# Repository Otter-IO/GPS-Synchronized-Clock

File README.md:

# GPS-Synchronized-Clock
This is an FPGA based GPS Synchronized Clock. It utilizes an Intel 10M02SCE144 single supply FPGA with integrated configuration memory.

The clock is split into 2 pieces, the FPGA board and the clock display. This was done so that to FPGA board could be used for other projects easily without redesign. It also allowed me to use a 4-layer board for the FPGA and a 2-layer board for the clock display. This helped keep costs low while also getting the advantages of a 4-layer board for the FPGA. The boards were designed using KiCAD.

The code is written in Verilog and is split into multiple modules to allow for easy modification and reuse. The bitstream files for the FPGA were generated using the free version of Intel Quartus Prime. The entire project is included for your use.

The code is by no means perfect. I’m still learning Verilog and there are certainly optimizations that could be made, especially with the SDC timing file. If you have more experience with FPGAs feel free to improve the design.

See the final product on YouTube: https://www.youtube.com/watch?v=TpDHRGk3vro

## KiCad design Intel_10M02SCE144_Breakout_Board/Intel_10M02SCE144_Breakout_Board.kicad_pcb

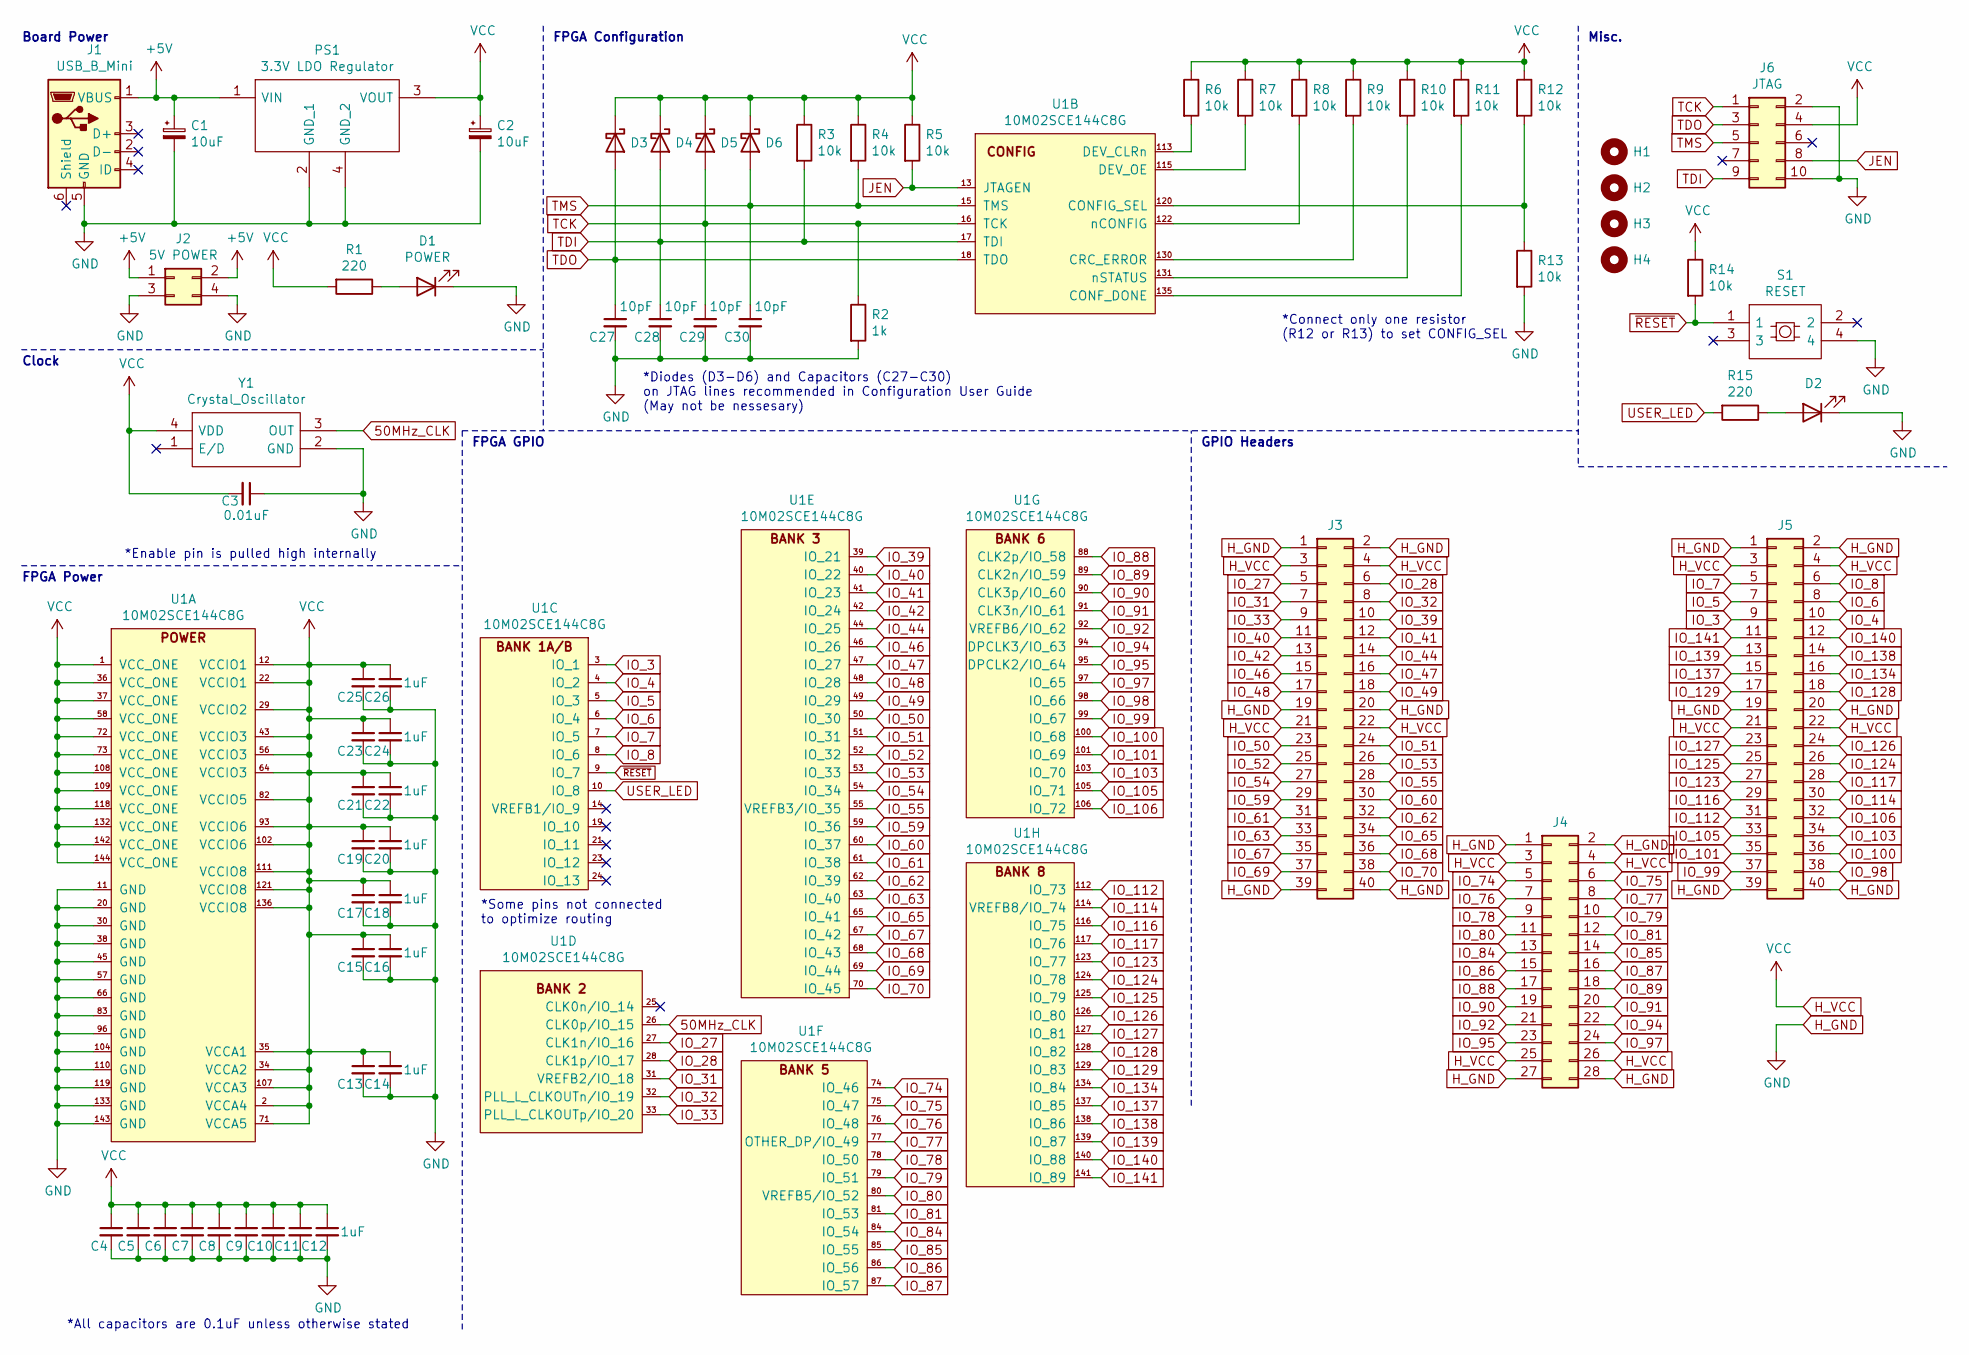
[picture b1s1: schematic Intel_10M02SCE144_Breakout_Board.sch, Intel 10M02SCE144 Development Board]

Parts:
C1, C2: 10uF; CP_Radial_D4.0mm_P2.00mm
C3: 0.01uF; C_0603_1608Metric_Pad1.08x0.95mm_HandSolder
C4, C5, C6, C7, C8, C9, C10, C11, C13, C15, C17, C19, C21, C23, C25: 0.1uF; C_0603_1608Metric_Pad1.08x0.95mm_HandSolder
C12, C14, C16, C18, C20, C22, C24, C26: 1uF; C_0603_1608Metric_Pad1.08x0.95mm_HandSolder
C27, C28, C29, C30: 10pF; C_0603_1608Metric_Pad1.08x0.95mm_HandSolder
D1: POWER; LED_D3.0mm
D2: LED; LED_D3.0mm
D3, D4, D5, D6: D_Schottky; D_0603_1608Metric_Pad1.05x0.95mm_HandSolder
H1, H2, H3, H4: MountingHole; MountingHole_3.2mm_M3
J1: USB_B_Mini; USB_Mini_Through_Hole
J2: 5V POWER; PinHeader_2x02_P2.54mm_Vertical
J3, J5: Conn_02x20_Odd_Even; PinHeader_2x20_P2.54mm_Vertical
J4: Conn_02x14_Odd_Even; PinHeader_2x14_P2.54mm_Vertical
J6: JTAG; PinHeader_2x05_P2.54mm_Vertical
PS1: 3.3V LDO Regulator; SOT230P700X190-4N
R1, R15: 220; R_0603_1608Metric_Pad0.98x0.95mm_HandSolder
R2: 1k; R_0603_1608Metric_Pad0.98x0.95mm_HandSolder
R3, R4, R5, R6, R7, R8, R9, R10, R11, R12, R13, R14: 10k; R_0603_1608Metric_Pad0.98x0.95mm_HandSolder
S1: RESET; THT_Tact_Switch
U1: 10M02SCE144C8G; QFP50P2200X2200X165-144N; Part Number 10M02SCE144C8G
Y1: Crystal_Oscillator; 7x5_Crystal_Oscillator

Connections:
50MHz_CLK: U1.26 (CLK0p/IO_15), Y1.3 (OUT)
+5V: C1.1, J1.1 (VBUS), J2.1, J2.2, PS1.1 (VIN)
H_GND: C1.2, C2.2, C3.1, C4.2, C5.2, C6.2, C7.2, C8.2, C9.2, C10.2, C11.2, C12.2, C13.2, C14.2, C15.2, C16.2, C17.2, C18.2, C19.2, C20.2, C21.2, C22.2, C23.2, C24.2, C25.2, C26.2, C27.2, C28.2, C29.2, C30.2, D1.1 (K), D2.1 (K), J1.5 (GND), J2.3, J2.4, J3.1, J3.2, J3.19, J3.20, J3.39, J3.40, J4.1, J4.2, J4.27, J4.28, J5.1, J5.2, J5.19, J5.20, J5.39, J5.40, J6.2, J6.10, PS1.2 (GND_1), PS1.4 (GND_2), R2.2, R13.2, S1.4, U1.11 (GND), U1.20 (GND), U1.30 (GND), U1.38 (GND), U1.45 (GND), U1.57 (GND), U1.66 (GND), U1.83 (GND), U1.96 (GND), U1.104 (GND), U1.110 (GND), U1.119 (GND), U1.133 (GND), U1.143 (GND), Y1.2 (GND)
H_VCC: C2.1, C3.2, C4.1, C5.1, C6.1, C7.1, C8.1, C9.1, C10.1, C11.1, C12.1, C13.1, C14.1, C15.1, C16.1, C17.1, C18.1, C19.1, C20.1, C21.1, C22.1, C23.1, C24.1, C25.1, C26.1, D3.1 (K), D4.1 (K), D5.1 (K), D6.1 (K), J3.3, J3.4, J3.21, J3.22, J4.3, J4.4, J4.25, J4.26, J5.3, J5.4, J5.21, J5.22, J6.4, PS1.3 (VOUT), R1.2, R3.1, R4.1, R5.1, R6.1, R7.1, R8.1, R9.1, R10.1, R11.1, R12.1, R14.1, U1.1 (VCC_ONE), U1.2 (VCCA4), U1.12 (VCCIO1), U1.22 (VCCIO1), U1.29 (VCCIO2), U1.34 (VCCA2), U1.35 (VCCA1), U1.36 (VCC_ONE), U1.37 (VCC_ONE), U1.43 (VCCIO3), U1.56 (VCCIO3), U1.58 (VCC_ONE), U1.64 (VCCIO3), U1.71 (VCCA5), U1.72 (VCC_ONE), U1.73 (VCC_ONE), U1.82 (VCCIO5), U1.93 (VCCIO6), U1.102 (VCCIO6), U1.107 (VCCA3), U1.108 (VCC_ONE), U1.109 (VCC_ONE), U1.111 (VCCIO8), U1.118 (VCC_ONE), U1.121 (VCCIO8), U1.132 (VCC_ONE), U1.136 (VCCIO8), U1.142 (VCC_ONE), U1.144 (VCC_ONE), Y1.4 (VDD)
IO_3: J5.9, U1.3 (IO_1)
IO_4: J5.10, U1.4 (IO_2)
IO_5: J5.7, U1.5 (IO_3)
IO_6: J5.8, U1.6 (IO_4)
IO_7: J5.5, U1.7 (IO_5)
IO_8: J5.6, U1.8 (IO_6)
IO_27: J3.5, U1.27 (CLK1n/IO_16)
IO_28: J3.6, U1.28 (CLK1p/IO_17)
IO_31: J3.7, U1.31 (VREFB2/IO_18)
IO_32: J3.8, U1.32 (PLL_L_CLKOUTn/IO_19)
IO_33: J3.9, U1.33 (PLL_L_CLKOUTp/IO_20)
IO_39: J3.10, U1.39 (IO_21)
IO_40: J3.11, U1.40 (IO_22)
IO_41: J3.12, U1.41 (IO_23)
IO_42: J3.13, U1.42 (IO_24)
IO_44: J3.14, U1.44 (IO_25)
IO_46: J3.15, U1.46 (IO_26)
IO_47: J3.16, U1.47 (IO_27)
IO_48: J3.17, U1.48 (IO_28)
IO_49: J3.18, U1.49 (IO_29)
IO_50: J3.23, U1.50 (IO_30)
IO_51: J3.24, U1.51 (IO_31)
IO_52: J3.25, U1.52 (IO_32)
IO_53: J3.26, U1.53 (IO_33)
IO_54: J3.27, U1.54 (IO_34)
IO_55: J3.28, U1.55 (VREFB3/IO_35)
IO_59: J3.29, U1.59 (IO_36)
IO_60: J3.30, U1.60 (IO_37)
IO_61: J3.31, U1.61 (IO_38)
IO_62: J3.32, U1.62 (IO_39)
IO_63: J3.33, U1.63 (IO_40)
IO_65: J3.34, U1.65 (IO_41)
IO_67: J3.35, U1.67 (IO_42)
IO_68: J3.36, U1.68 (IO_43)
IO_69: J3.37, U1.69 (IO_44)
IO_70: J3.38, U1.70 (IO_45)
IO_74: J4.5, U1.74 (IO_46)
IO_75: J4.6, U1.75 (IO_47)
IO_76: J4.7, U1.76 (IO_48)
IO_77: J4.8, U1.77 (OTHER_DP/IO_49)
IO_78: J4.9, U1.78 (IO_50)
IO_79: J4.10, U1.79 (IO_51)
IO_80: J4.11, U1.80 (VREFB5/IO_52)
IO_81: J4.12, U1.81 (IO_53)
IO_84: J4.13, U1.84 (IO_54)
IO_85: J4.14, U1.85 (IO_55)
IO_86: J4.15, U1.86 (IO_56)
IO_87: J4.16, U1.87 (IO_57)
IO_88: J4.17, U1.88 (CLK2p/IO_58)
IO_89: J4.18, U1.89 (CLK2n/IO_59)
IO_90: J4.19, U1.90 (CLK3p/IO_60)
IO_91: J4.20, U1.91 (CLK3n/IO_61)
IO_92: J4.21, U1.92 (VREFB6/IO_62)
IO_94: J4.22, U1.94 (DPCLK3/IO_63)
IO_95: J4.23, U1.95 (DPCLK2/IO_64)
IO_97: J4.24, U1.97 (IO_65)
IO_98: J5.38, U1.98 (IO_66)
IO_99: J5.37, U1.99 (IO_67)
IO_100: J5.36, U1.100 (IO_68)
IO_101: J5.35, U1.101 (IO_69)
IO_103: J5.34, U1.103 (IO_70)
IO_105: J5.33, U1.105 (IO_71)
IO_106: J5.32, U1.106 (IO_72)
IO_112: J5.31, U1.112 (IO_73)
IO_114: J5.30, U1.114 (VREFB8/IO_74)
IO_116: J5.29, U1.116 (IO_75)
IO_117: J5.28, U1.117 (IO_76)
IO_123: J5.27, U1.123 (IO_77)
IO_124: J5.26, U1.124 (IO_78)
IO_125: J5.25, U1.125 (IO_79)
IO_126: J5.24, U1.126 (IO_80)
IO_127: J5.23, U1.127 (IO_81)
IO_128: J5.18, U1.128 (IO_82)
IO_129: J5.17, U1.129 (IO_83)
IO_134: J5.16, U1.134 (IO_84)
IO_137: J5.15, U1.137 (IO_85)
IO_138: J5.14, U1.138 (IO_86)
IO_139: J5.13, U1.139 (IO_87)
IO_140: J5.12, U1.140 (IO_88)
IO_141: J5.11, U1.141 (IO_89)
JEN: J6.8, R5.2, U1.13 (JTAGEN)
unnamed: D1.2 (A), R1.1
unnamed: D2.2 (A), R15.1
unnamed: R6.2, U1.113 (DEV_CLRn)
unnamed: R7.2, U1.115 (DEV_OE)
unnamed: R8.2, U1.122 (nCONFIG)
unnamed: R9.2, U1.130 (CRC_ERROR)
unnamed: R10.2, U1.131 (nSTATUS)
unnamed: R11.2, U1.135 (CONF_DONE)
unnamed: R12.2, R13.1, U1.120 (CONFIG_SEL)
TCK: C29.1, D5.2 (A), J6.1, R2.1, U1.16 (TCK)
TDI: C28.1, D4.2 (A), J6.9, R3.2, U1.17 (TDI)
TDO: C27.1, D3.2 (A), J6.3, U1.18 (TDO)
TMS: C30.1, D6.2 (A), J6.5, R4.2, U1.15 (TMS)
USER_LED: R15.2, U1.10 (IO_8)
~RESET: R14.2, S1.1, U1.9 (IO_7)

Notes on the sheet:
*Enable pin is pulled high internally
*All capacitors are 0.1uF unless otherwise stated
*Connect only one resistor (R12 or R13) to set CONFIG_SEL
*Diodes (D3-D6) and Capacitors (C27-C30) on JTAG lines recommended in Configuration User Guide (May not be nessesary)
*Some pins not connected to optimize routing
Board Power
Clock
FPGA Power
FPGA GPIO
FPGA Configuration
GPIO Headers
Misc.

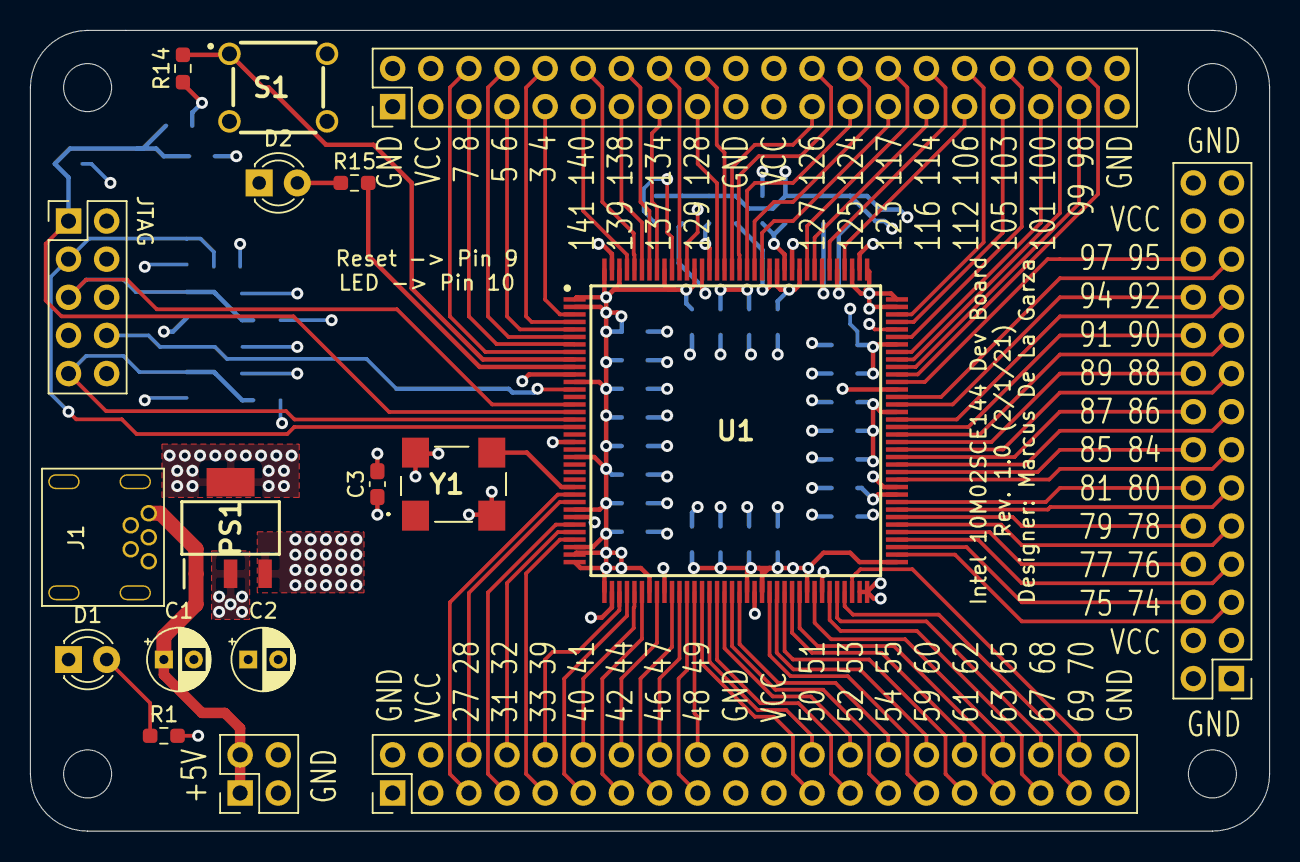
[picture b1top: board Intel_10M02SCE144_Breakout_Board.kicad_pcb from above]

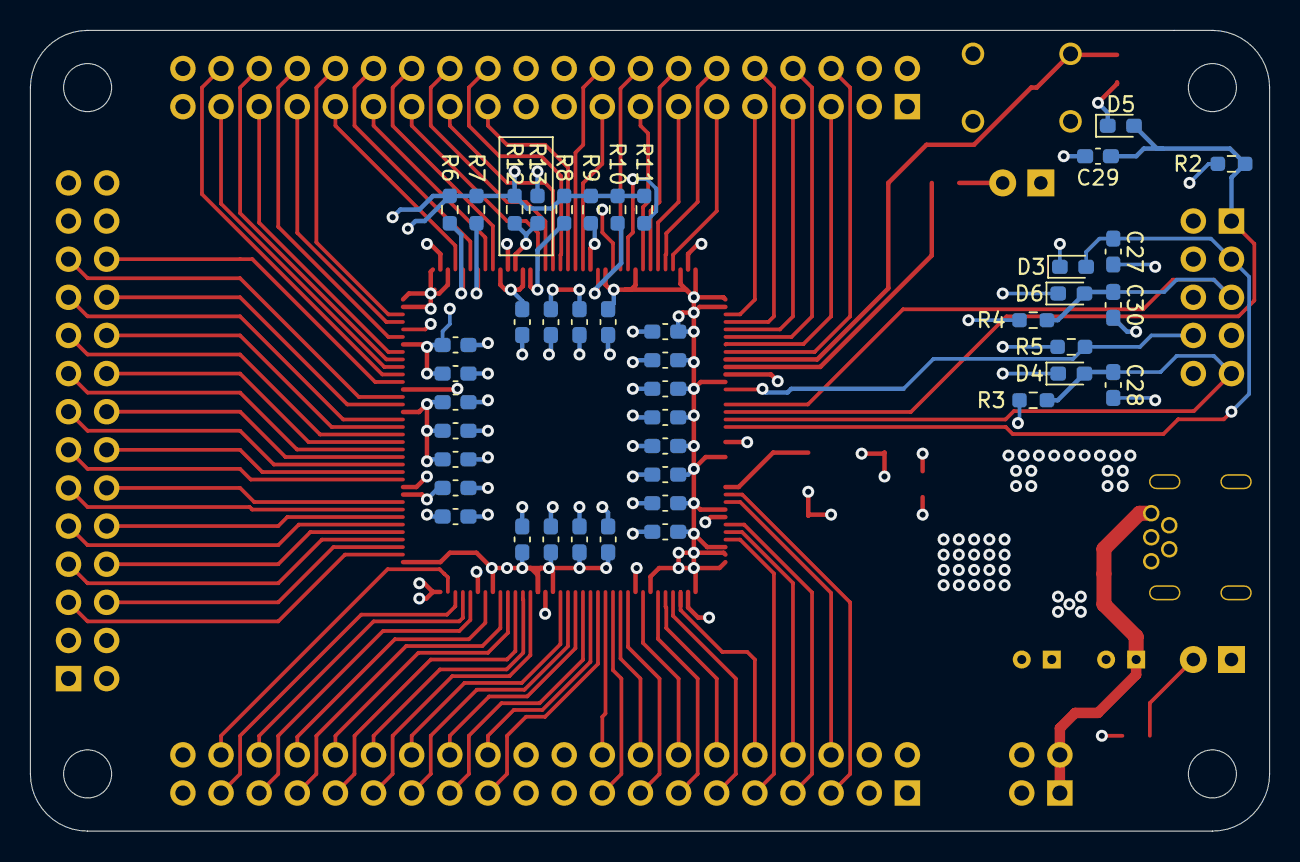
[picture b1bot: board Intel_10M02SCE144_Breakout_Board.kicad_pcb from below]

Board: 4 copper layers, 82.5 x 53.3 mm, 65 parts (43 on the bottom side), 100 nets.

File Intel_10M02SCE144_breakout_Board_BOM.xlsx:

Ref | Value | Description | KiCAD Footprint
C1 | 10uF | Electrolytic Through Hole Capacitor | Capacitor_THT:CP_Radial_D4.0mm_P2.00mm
C10 | 0.1uF | 0603 Ceramic Capacitor | Capacitor_SMD:C_0603_1608Metric_Pad1.08x0.95mm_HandSolder
C11 | 0.1uF | 0603 Ceramic Capacitor | Capacitor_SMD:C_0603_1608Metric_Pad1.08x0.95mm_HandSolder
C12 | 1uF | 0603 Ceramic Capacitor | Capacitor_SMD:C_0603_1608Metric_Pad1.08x0.95mm_HandSolder
C13 | 0.1uF | 0603 Ceramic Capacitor | Capacitor_SMD:C_0603_1608Metric_Pad1.08x0.95mm_HandSolder
C14 | 1uF | 0603 Ceramic Capacitor | Capacitor_SMD:C_0603_1608Metric_Pad1.08x0.95mm_HandSolder
C15 | 0.1uF | 0603 Ceramic Capacitor | Capacitor_SMD:C_0603_1608Metric_Pad1.08x0.95mm_HandSolder
C16 | 1uF | 0603 Ceramic Capacitor | Capacitor_SMD:C_0603_1608Metric_Pad1.08x0.95mm_HandSolder
C17 | 0.1uF | 0603 Ceramic Capacitor | Capacitor_SMD:C_0603_1608Metric_Pad1.08x0.95mm_HandSolder
C18 | 1uF | 0603 Ceramic Capacitor | Capacitor_SMD:C_0603_1608Metric_Pad1.08x0.95mm_HandSolder
C19 | 0.1uF | 0603 Ceramic Capacitor | Capacitor_SMD:C_0603_1608Metric_Pad1.08x0.95mm_HandSolder
C2 | 10uF | Electrolytic Through Hole Capacitor | Capacitor_THT:CP_Radial_D4.0mm_P2.00mm
C20 | 1uF | 0603 Ceramic Capacitor | Capacitor_SMD:C_0603_1608Metric_Pad1.08x0.95mm_HandSolder
C21 | 0.1uF | 0603 Ceramic Capacitor | Capacitor_SMD:C_0603_1608Metric_Pad1.08x0.95mm_HandSolder
C22 | 1uF | 0603 Ceramic Capacitor | Capacitor_SMD:C_0603_1608Metric_Pad1.08x0.95mm_HandSolder
C23 | 0.1uF | 0603 Ceramic Capacitor | Capacitor_SMD:C_0603_1608Metric_Pad1.08x0.95mm_HandSolder
C24 | 1uF | 0603 Ceramic Capacitor | Capacitor_SMD:C_0603_1608Metric_Pad1.08x0.95mm_HandSolder
C25 | 0.1uF | 0603 Ceramic Capacitor | Capacitor_SMD:C_0603_1608Metric_Pad1.08x0.95mm_HandSolder
C26 | 1uF | 0603 Ceramic Capacitor | Capacitor_SMD:C_0603_1608Metric_Pad1.08x0.95mm_HandSolder
C27 | 10pF | 0603 Ceramic Capacitor | Capacitor_SMD:C_0603_1608Metric_Pad1.08x0.95mm_HandSolder
C28 | 10pF | 0603 Ceramic Capacitor | Capacitor_SMD:C_0603_1608Metric_Pad1.08x0.95mm_HandSolder
C29 | 10pF | 0603 Ceramic Capacitor | Capacitor_SMD:C_0603_1608Metric_Pad1.08x0.95mm_HandSolder
C3 | 0.01uF | 0603 Ceramic Capacitor | Capacitor_SMD:C_0603_1608Metric_Pad1.08x0.95mm_HandSolder
C30 | 10pF | 0603 Ceramic Capacitor | Capacitor_SMD:C_0603_1608Metric_Pad1.08x0.95mm_HandSolder
C4 | 0.1uF | 0603 Ceramic Capacitor | Capacitor_SMD:C_0603_1608Metric_Pad1.08x0.95mm_HandSolder
C5 | 0.1uF | 0603 Ceramic Capacitor | Capacitor_SMD:C_0603_1608Metric_Pad1.08x0.95mm_HandSolder
C6 | 0.1uF | 0603 Ceramic Capacitor | Capacitor_SMD:C_0603_1608Metric_Pad1.08x0.95mm_HandSolder
C7 | 0.1uF | 0603 Ceramic Capacitor | Capacitor_SMD:C_0603_1608Metric_Pad1.08x0.95mm_HandSolder
C8 | 0.1uF | 0603 Ceramic Capacitor | Capacitor_SMD:C_0603_1608Metric_Pad1.08x0.95mm_HandSolder
C9 | 0.1uF | 0603 Ceramic Capacitor | Capacitor_SMD:C_0603_1608Metric_Pad1.08x0.95mm_HandSolder
D1 | POWER | 3mm LED | LED_THT:LED_D3.0mm
D2 | LED | 3mm LED | LED_THT:LED_D3.0mm
D3 | D_Schottky | 0603 Schottky diode | Diode_SMD:D_0603_1608Metric_Pad1.05x0.95mm_HandSolder
D4 | D_Schottky | 0603 Schottky diode | Diode_SMD:D_0603_1608Metric_Pad1.05x0.95mm_HandSolder
D5 | D_Schottky | 0603 Schottky diode | Diode_SMD:D_0603_1608Metric_Pad1.05x0.95mm_HandSolder
D6 | D_Schottky | 0603 Schottky diode | Diode_SMD:D_0603_1608Metric_Pad1.05x0.95mm_HandSolder
H1 | MountingHole | M3 Mounting Hole | MountingHole:MountingHole_3.2mm_M3
H2 | MountingHole | M3 Mounting Hole | MountingHole:MountingHole_3.2mm_M3
H3 | MountingHole | M3 Mounting Hole | MountingHole:MountingHole_3.2mm_M3
H4 | MountingHole | M3 Mounting Hole | MountingHole:MountingHole_3.2mm_M3
J1 | USB_B_Mini | USB Mini Type B connector | Custom_Parts:USB_Mini_Through_Hole
J2 | 5V POWER | 2.54mm Male Pin Headers | Connector_PinHeader_2.54mm:PinHeader_2x02_P2.54mm_Vertical
J3 | IO Pins | 2.54mm Male Pin Headers | Connector_PinHeader_2.54mm:PinHeader_2x20_P2.54mm_Vertical
J4 | IO Pins | 2.54mm Male Pin Headers | Connector_PinHeader_2.54mm:PinHeader_2x14_P2.54mm_Vertical
J5 | IO Pins | 2.54mm Male Pin Headers | Connector_PinHeader_2.54mm:PinHeader_2x20_P2.54mm_Vertical
J6 | JTAG | 2.54mm Male Pin Headers | Connector_PinHeader_2.54mm:PinHeader_2x05_P2.54mm_Vertical
PS1 | 3.3V LDO Regulator | SOT-223 3.3V Linear Regulator (PAM3110ABA330R) | Custom_Parts:SOT230P700X190-4N
R1 | 220 | 0603 Resistor | Resistor_SMD:R_0603_1608Metric_Pad0.98x0.95mm_HandSolder
R10 | 10k | 0603 Resistor | Resistor_SMD:R_0603_1608Metric_Pad0.98x0.95mm_HandSolder
R11 | 10k | 0603 Resistor | Resistor_SMD:R_0603_1608Metric_Pad0.98x0.95mm_HandSolder
R12 | 10k | 0603 Resistor | Resistor_SMD:R_0603_1608Metric_Pad0.98x0.95mm_HandSolder
R13 | 10k | 0603 Resistor | Resistor_SMD:R_0603_1608Metric_Pad0.98x0.95mm_HandSolder
R14 | 10k | 0603 Resistor | Resistor_SMD:R_0603_1608Metric_Pad0.98x0.95mm_HandSolder
R15 | 220 | 0603 Resistor | Resistor_SMD:R_0603_1608Metric_Pad0.98x0.95mm_HandSolder
R2 | 1k | 0603 Resistor | Resistor_SMD:R_0603_1608Metric_Pad0.98x0.95mm_HandSolder
R3 | 10k | 0603 Resistor | Resistor_SMD:R_0603_1608Metric_Pad0.98x0.95mm_HandSolder
R4 | 10k | 0603 Resistor | Resistor_SMD:R_0603_1608Metric_Pad0.98x0.95mm_HandSolder
R5 | 10k | 0603 Resistor | Resistor_SMD:R_0603_1608Metric_Pad0.98x0.95mm_HandSolder
R6 | 10k | 0603 Resistor | Resistor_SMD:R_0603_1608Metric_Pad0.98x0.95mm_HandSolder
R7 | 10k | 0603 Resistor | Resistor_SMD:R_0603_1608Metric_Pad0.98x0.95mm_HandSolder
R8 | 10k | 0603 Resistor | Resistor_SMD:R_0603_1608Metric_Pad0.98x0.95mm_HandSolder
R9 | 10k | 0603 Resistor | Resistor_SMD:R_0603_1608Metric_Pad0.98x0.95mm_HandSolder
S1 | RESET | Generic Tact Switch | Custom_Parts:THT_Tact_Switch
U1 | 10M02SCE144C8G | Intel 10M02SCE144C8G EQFP-144 FPGA | Intel_MAX10_FPGA:QFP50P2200X2200X165-144N
Y1 | 50MHz 3.3V | 7mmx5mm 50MHz 3.3V Clock Oscillator (XLH735050.000000X) | Custom_Parts:7x5_Crystal_Oscillator
